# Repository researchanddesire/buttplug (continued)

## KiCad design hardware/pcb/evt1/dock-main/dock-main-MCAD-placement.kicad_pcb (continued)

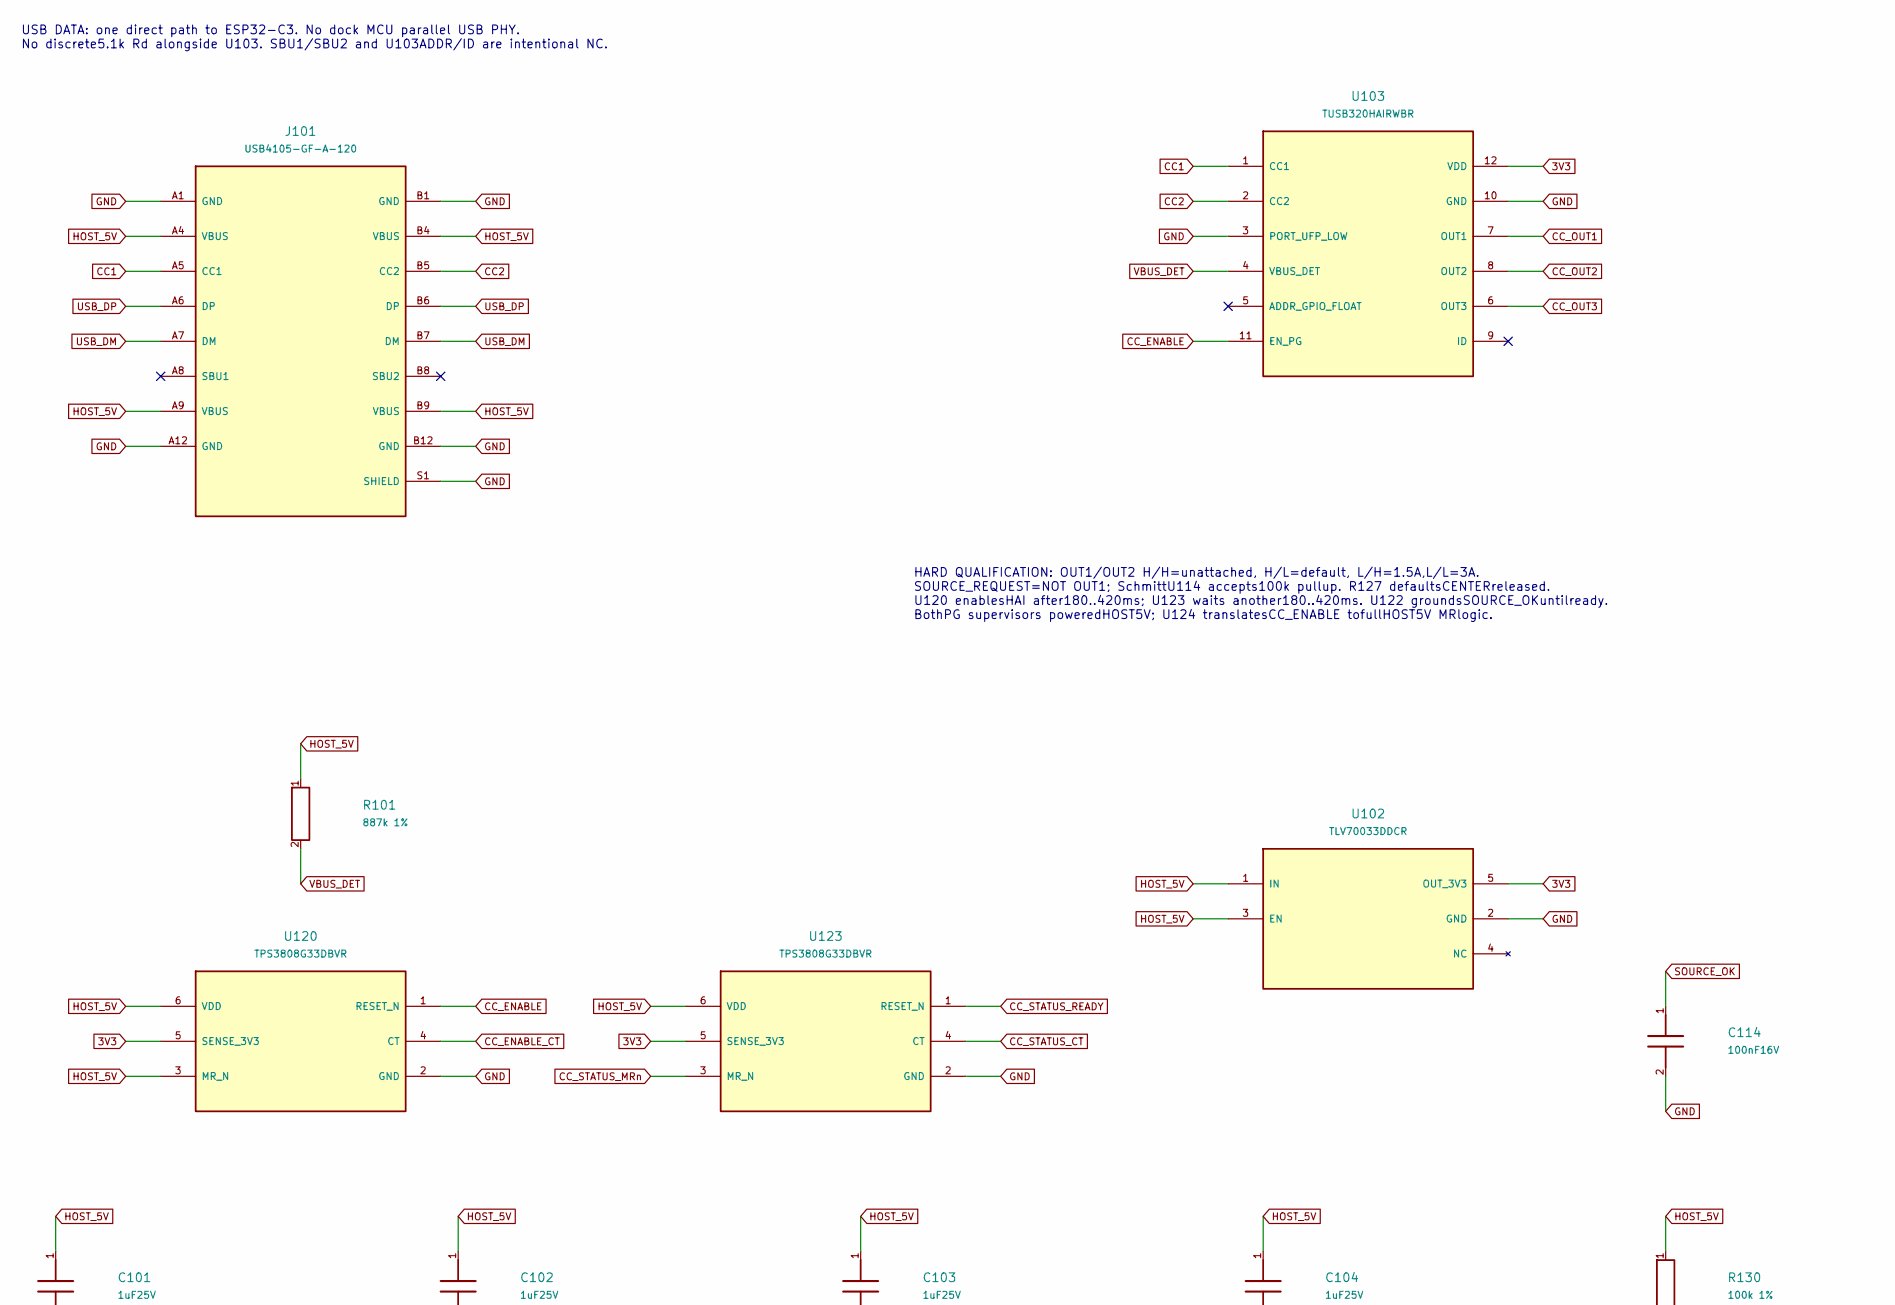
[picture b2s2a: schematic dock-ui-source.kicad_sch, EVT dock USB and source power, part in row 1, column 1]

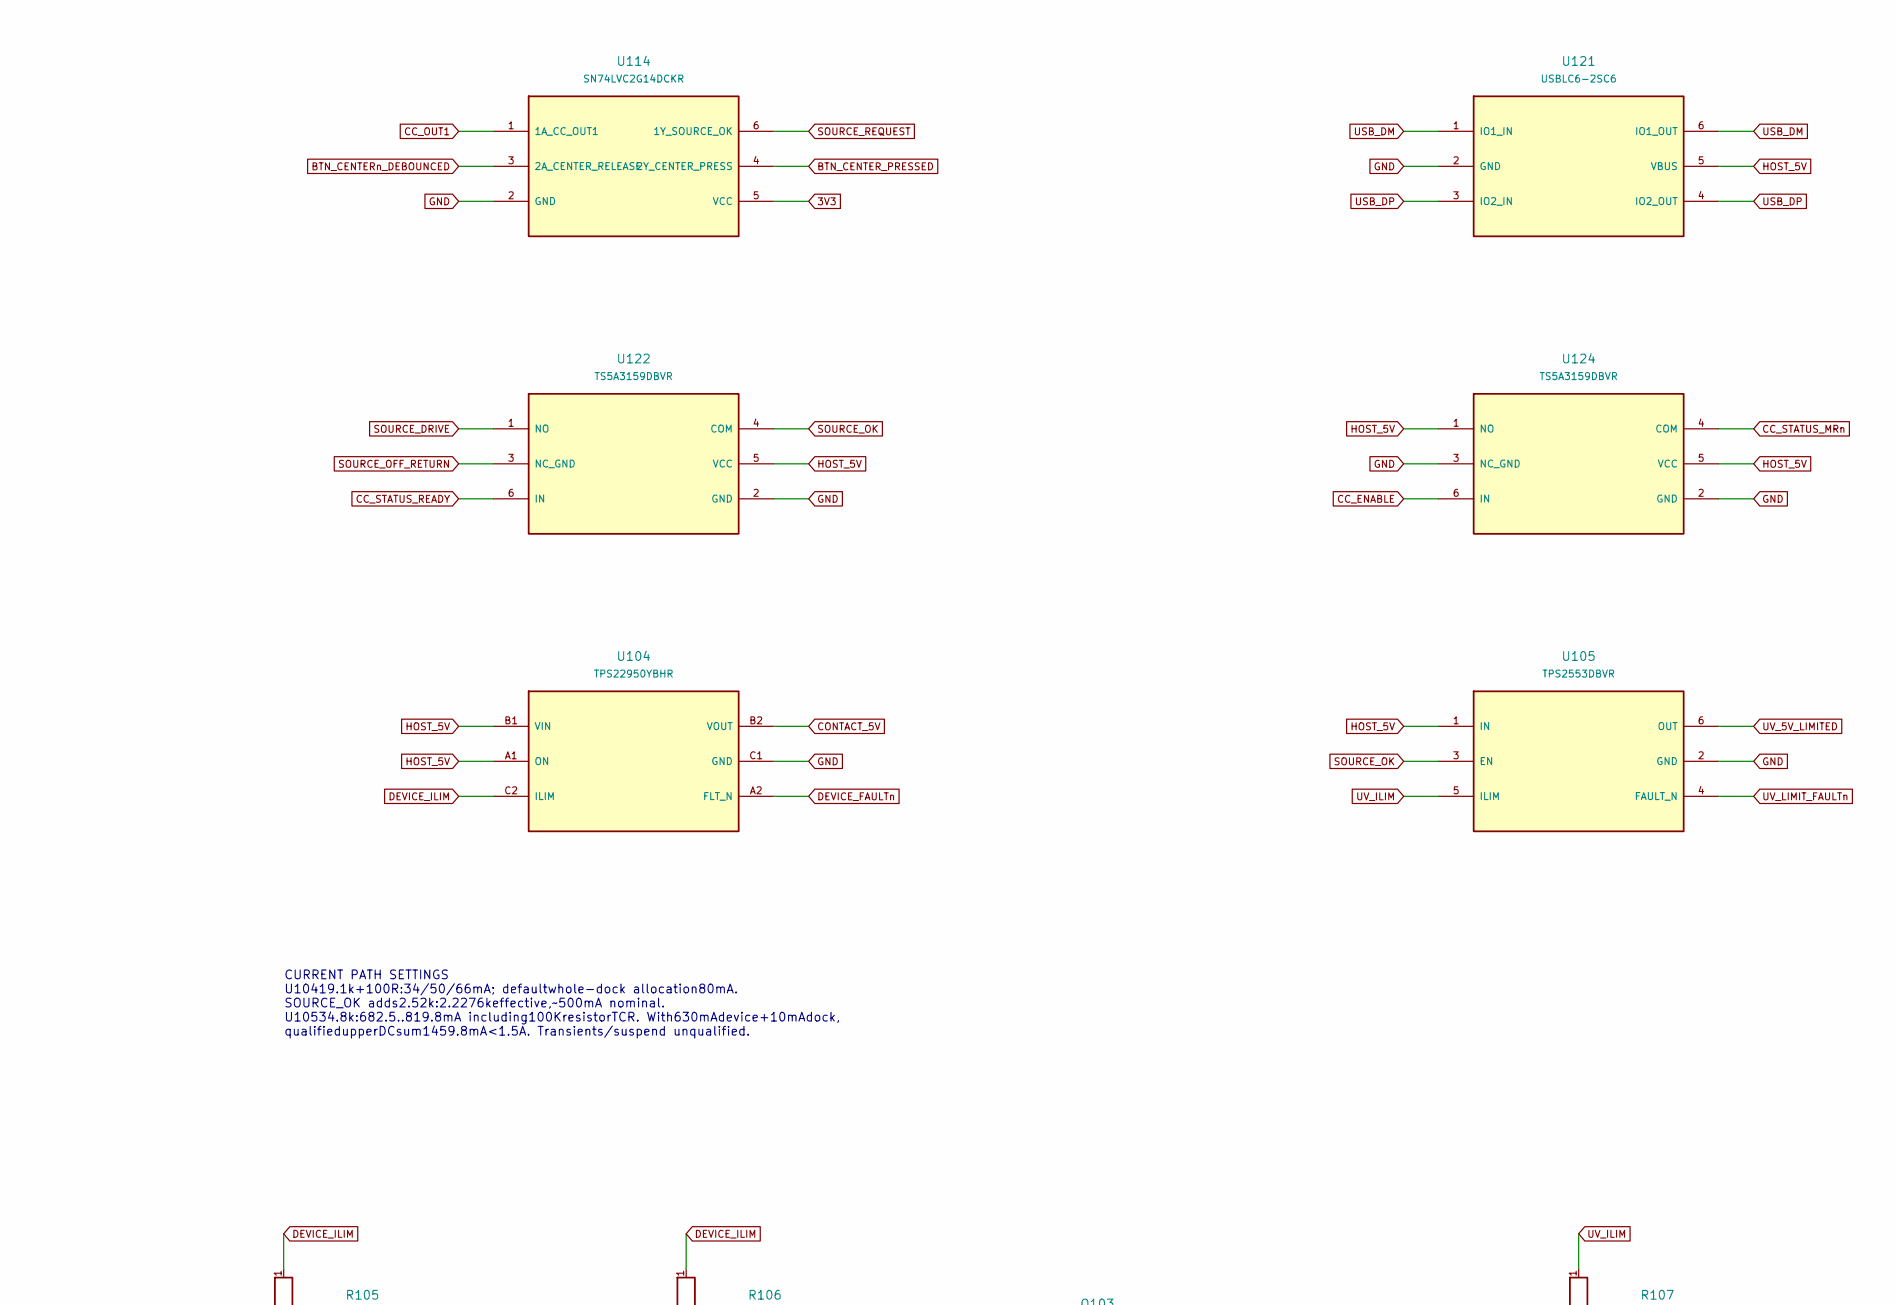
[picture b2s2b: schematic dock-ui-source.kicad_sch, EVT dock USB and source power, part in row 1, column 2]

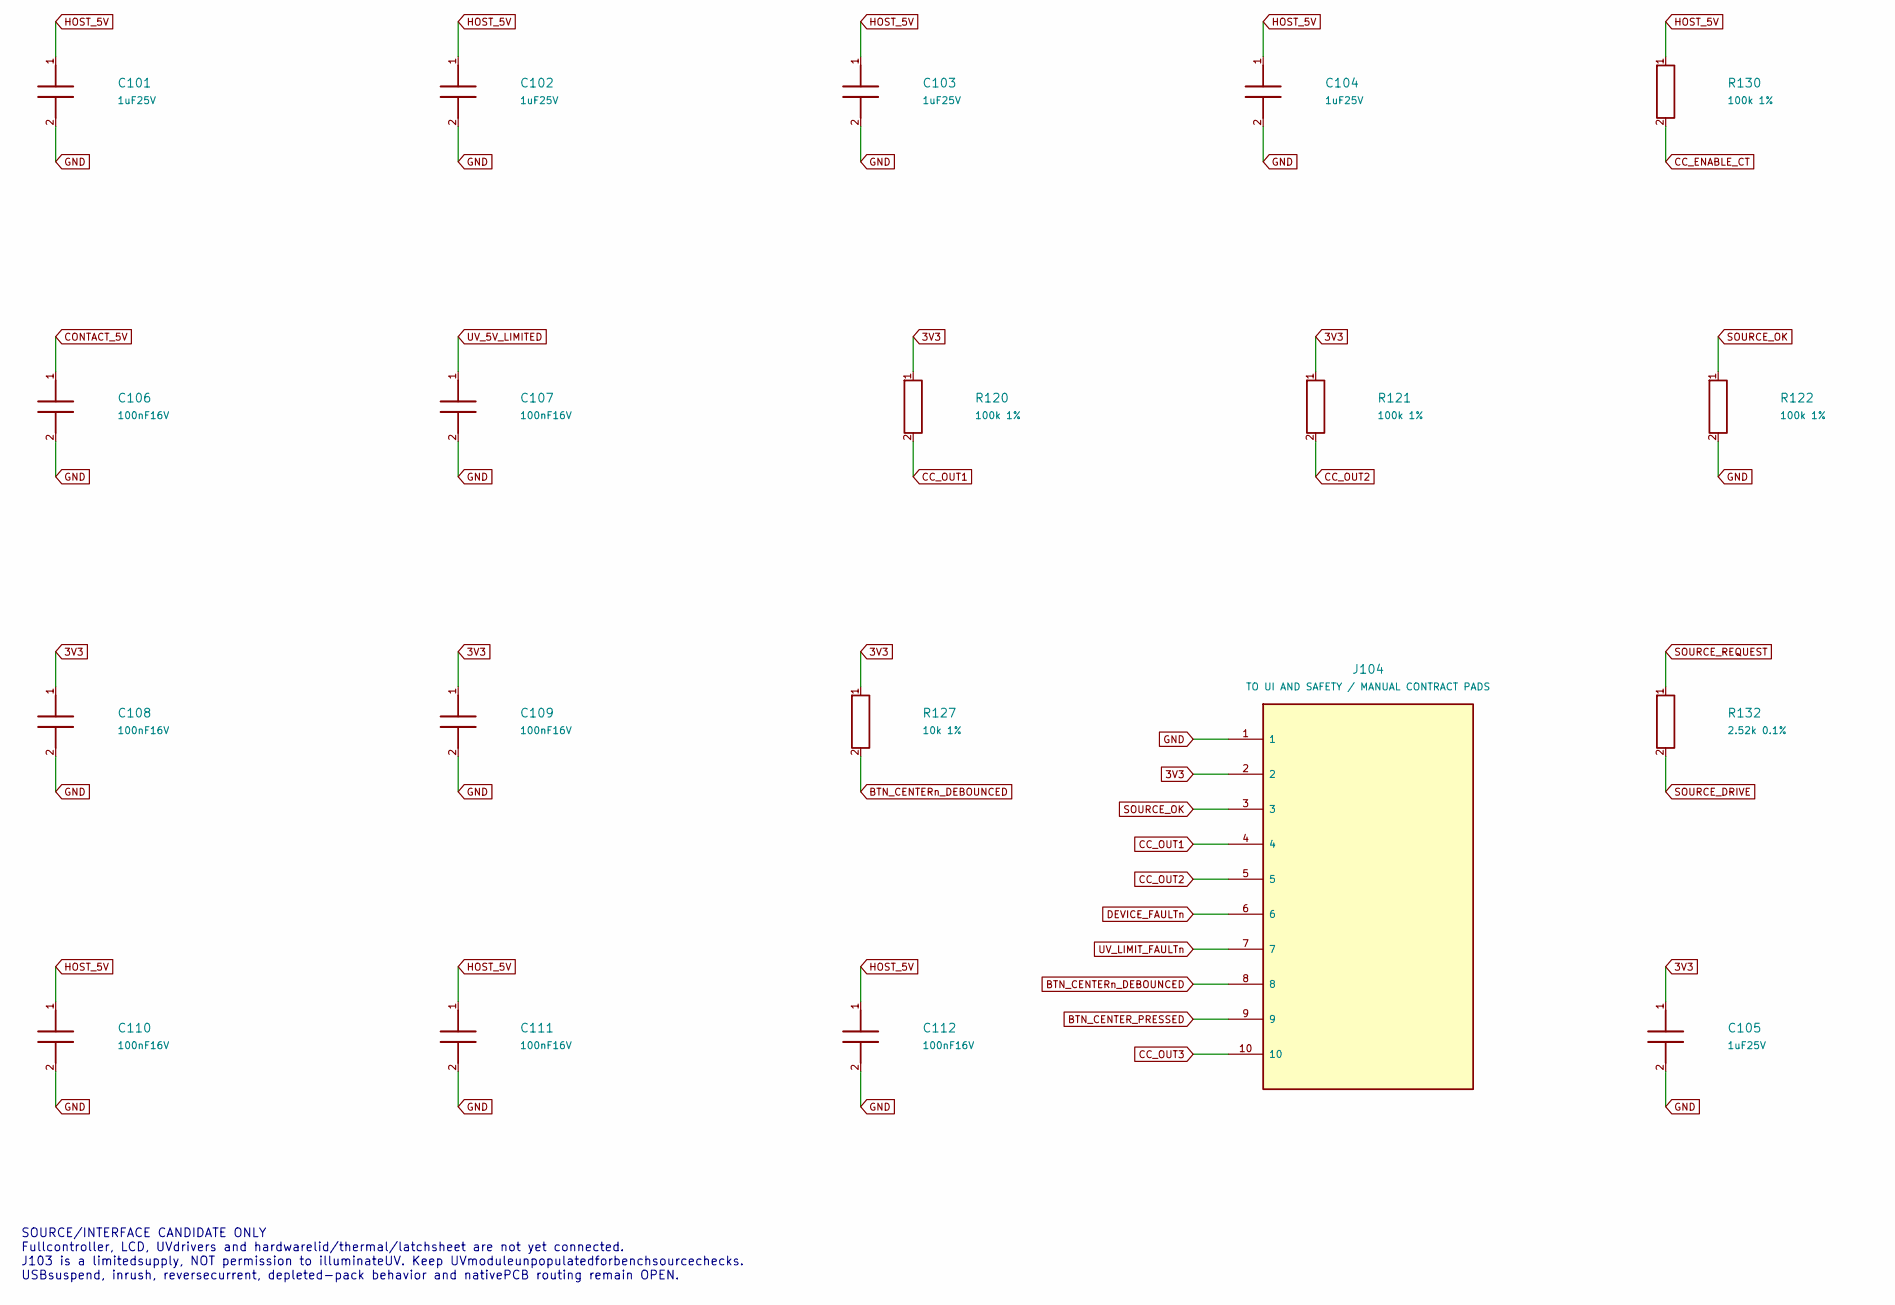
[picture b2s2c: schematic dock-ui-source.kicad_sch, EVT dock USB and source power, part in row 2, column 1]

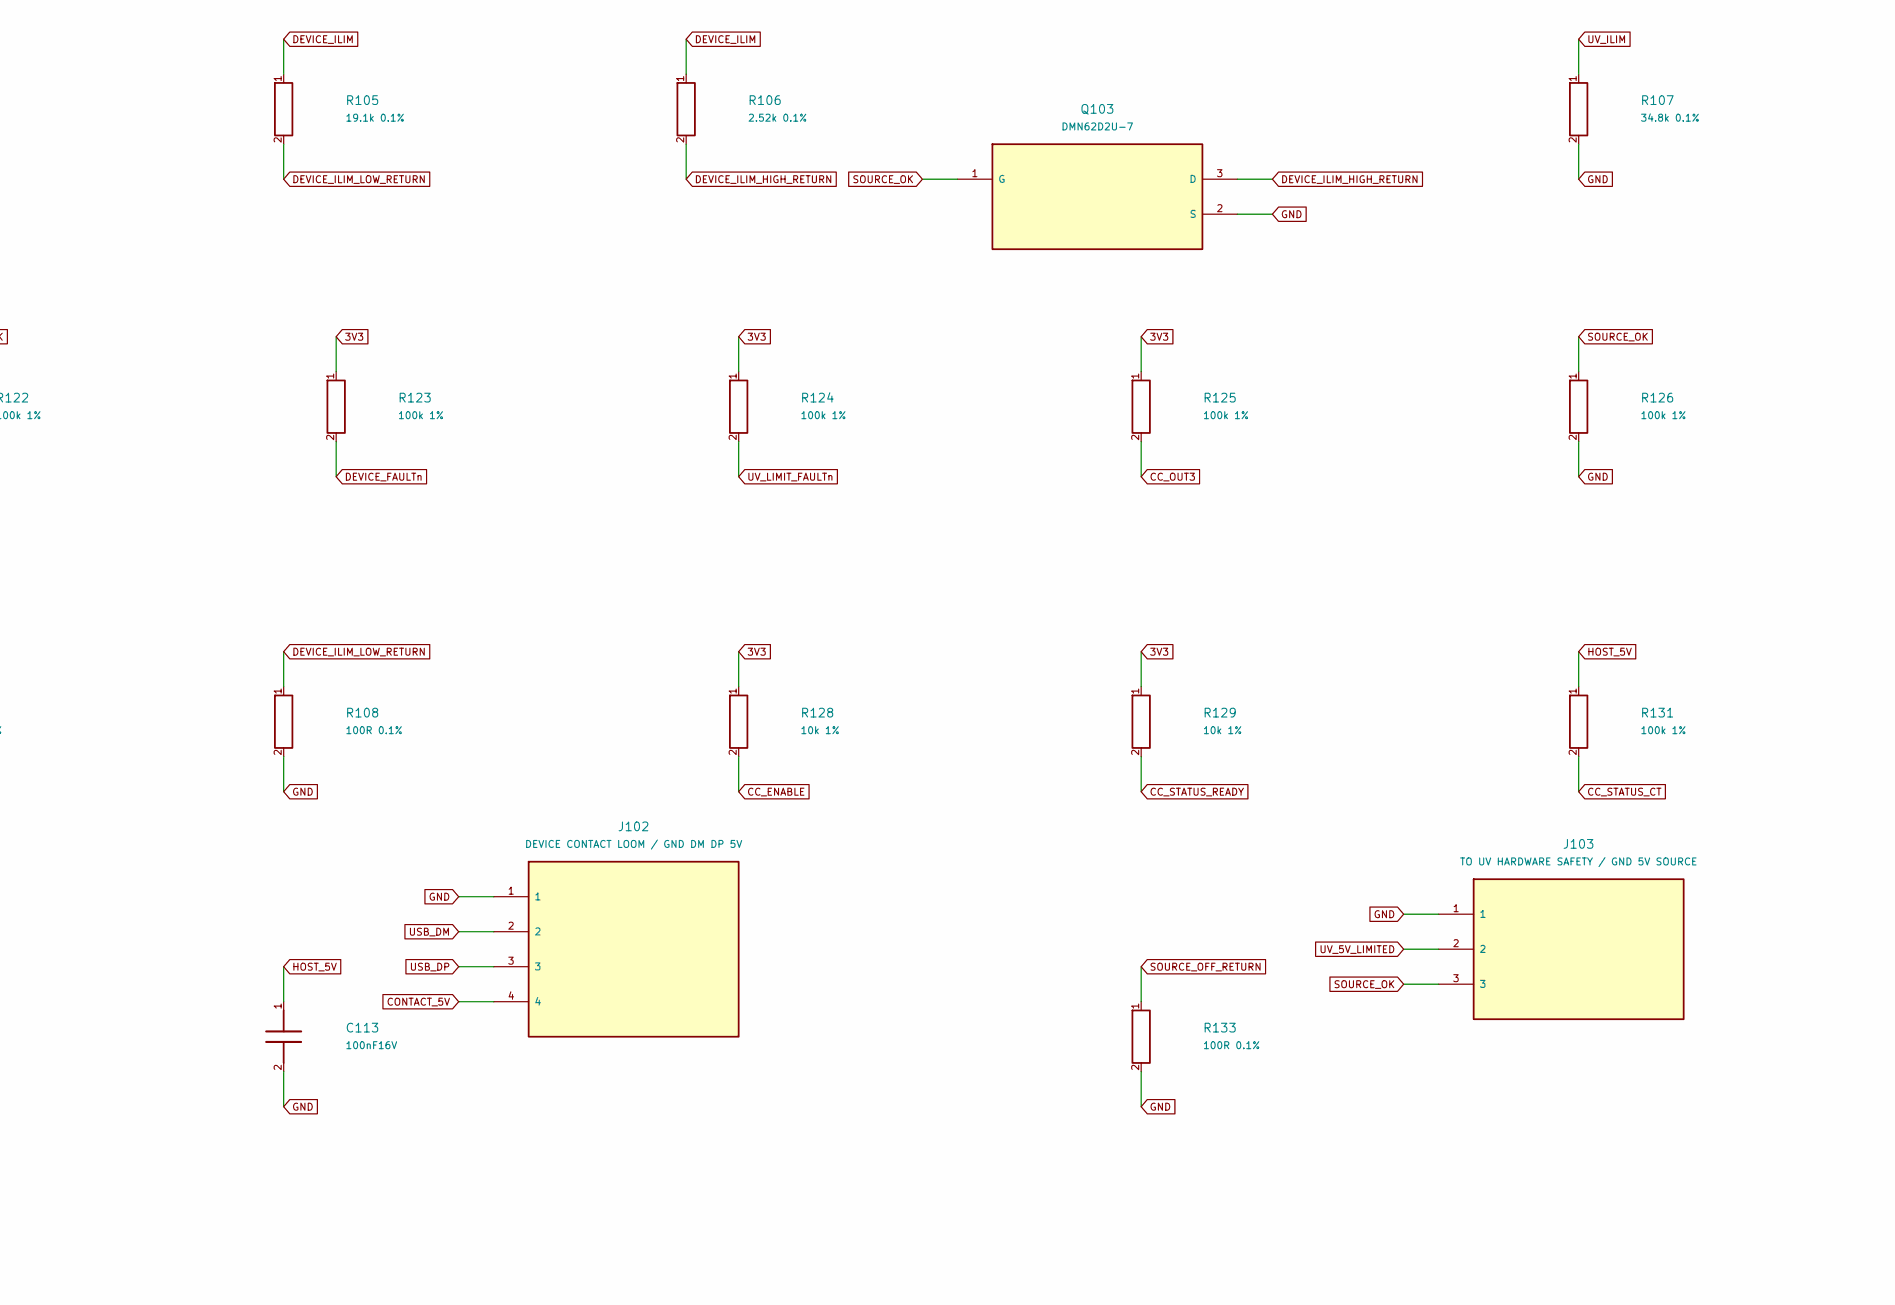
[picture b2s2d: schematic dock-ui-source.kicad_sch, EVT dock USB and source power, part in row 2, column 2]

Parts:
C101, C102, C103, C104, C105: 1uF25V; C_0603_1608Metric; MPN C1608X7R1E105K080AB
C106, C107, C108, C109, C110, C111, C112, C113, C114: 100nF16V; C_0402_1005Metric; MPN GRM155R71C104KA88D
J101: USB4105-GF-A-120; USB_C_Receptacle_GCT_USB4105-xx-A_16P_TopMnt_Horizontal; MPN USB4105-GF-A-120
J102: DEVICE CONTACT LOOM / GND DM DP 5V; Contact_Loom_4Land; MPN DEVICE CONTACT LOOM / GND DM DP 5V
J103: TO UV HARDWARE SAFETY / GND 5V SOURCE; Control_Loom_3Land; MPN TO UV HARDWARE SAFETY / GND 5V SOURCE
J104: TO UI AND SAFETY / MANUAL CONTRACT PADS; Control_Loom_10Land; MPN TO UI AND SAFETY / MANUAL CONTRACT PADS
Q103: DMN62D2U-7; SOT-23; MPN DMN62D2U-7
R101: 887k 1%; R_0603_1608Metric; MPN RC0603FR-07887KL
R105: 19.1k 0.1%; R_0603_1608Metric; MPN RT0603BRD0719K1L
R106, R132: 2.52k 0.1%; R_0603_1608Metric; MPN RT0603BRD072K52L
R107: 34.8k 0.1%; R_0603_1608Metric; MPN RT0603BRD0734K8L
R108, R133: 100R 0.1%; R_0603_1608Metric; MPN RT0603BRD07100RL
R120, R121, R122, R123, R124, R125, R126, R130, R131: 100k 1%; R_0603_1608Metric; MPN RC0603FR-07100KL
R127, R128, R129: 10k 1%; R_0603_1608Metric; MPN RC0603FR-0710KL
U102: TLV70033DDCR; TSOT-23-5; MPN TLV70033DDCR
U103: TUSB320HAIRWBR; Texas_X2QFN-12_1.6x1.6mm_P0.4mm; MPN TUSB320HAIRWBR
U104: TPS22950YBHR; Texas_YBH0006-C02_DSBGA-6_1.106x0.706mm_P0.4mm; MPN TPS22950YBHR
U105: TPS2553DBVR; SOT-23-6; MPN TPS2553DBVR
U114: SN74LVC2G14DCKR; SOT-363_SC-70-6; MPN SN74LVC2G14DCKR
U120, U123: TPS3808G33DBVR; SOT-23-6; MPN TPS3808G33DBVR
U121: USBLC6-2SC6; SOT-23-6; MPN USBLC6-2SC6
U122, U124: TS5A3159DBVR; SOT-23-6; MPN TS5A3159DBVR

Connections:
3V3: C105.1, C108.1, C109.1, J104.2, R120.1, R121.1, R123.1, R124.1, R125.1, R127.1, R128.1, R129.1, U102.5 (OUT_3V3), U103.12 (VDD), U114.5 (VCC), U120.5 (SENSE_3V3), U123.5 (SENSE_3V3); also elsewhere on the board
BTN_CENTER_PRESSED: J104.9, U114.4 (2Y_CENTER_PRESS); also elsewhere on the board
BTN_CENTERn_DEBOUNCED: J104.8, R127.2, U114.3 (2A_CENTER_RELEASE); also elsewhere on the board
CC1: J101.A5 (CC1), U103.1 (CC1)
CC2: J101.B5 (CC2), U103.2 (CC2)
CC_ENABLE: R128.2, U103.11 (EN_PG), U120.1 (RESET_N), U124.6 (IN)
CC_ENABLE_CT: R130.2, U120.4 (CT)
CC_OUT1: J104.4, R120.2, U103.7 (OUT1), U114.1 (1A_CC_OUT1); also elsewhere on the board
CC_OUT2: J104.5, R121.2, U103.8 (OUT2); also elsewhere on the board
CC_OUT3: J104.10, R125.2, U103.6 (OUT3)
CC_STATUS_CT: R131.2, U123.4 (CT)
CC_STATUS_MRn: U123.3 (MR_N), U124.4 (COM)
CC_STATUS_READY: R129.2, U122.6 (IN), U123.1 (RESET_N)
CONTACT_5V: C106.1, J102.4, U104.B2 (VOUT)
DEVICE_FAULTn: J104.6, R123.2, U104.A2 (FLT_N); also elsewhere on the board
DEVICE_ILIM: R105.1, R106.1, U104.C2 (ILIM)
DEVICE_ILIM_HIGH_RETURN: Q103.3 (D), R106.2
DEVICE_ILIM_LOW_RETURN: R105.2, R108.1
GND: C101.2, C102.2, C103.2, C104.2, C105.2, C106.2, C107.2, C108.2, C109.2, C110.2, C111.2, C112.2, C113.2, C114.2, J101.A1 (GND), J101.A12 (GND), J101.B1 (GND), J101.B12 (GND), J101.S1 (SHIELD), J102.1, J103.1, J104.1, Q103.2 (S), R107.2, R108.2, R122.2, R126.2, R133.2, U102.2 (GND), U103.3 (PORT_UFP_LOW), U103.10 (GND), U104.C1 (GND), U105.2 (GND), U114.2 (GND), U120.2 (GND), U121.2 (GND), U122.2 (GND), U123.2 (GND), U124.2 (GND), U124.3 (NC_GND); also elsewhere on the board
HOST_5V: C101.1, C102.1, C103.1, C104.1, C110.1, C111.1, C112.1, C113.1, J101.A4 (VBUS), J101.A9 (VBUS), J101.B4 (VBUS), J101.B9 (VBUS), R101.1, R130.1, R131.1, U102.1 (IN), U102.3 (EN), U104.A1 (ON), U104.B1 (VIN), U105.1 (IN), U120.3 (MR_N), U120.6 (VDD), U121.5 (VBUS), U122.5 (VCC), U123.6 (VDD), U124.1 (NO), U124.5 (VCC); also elsewhere on the board
SOURCE_DRIVE: R132.2, U122.1 (NO)
SOURCE_OFF_RETURN: R133.1, U122.3 (NC_GND)
SOURCE_OK: C114.1, J103.3, J104.3, Q103.1 (G), R122.1, R126.1, U105.3 (EN), U122.4 (COM); also elsewhere on the board
SOURCE_REQUEST: R132.1, U114.6 (1Y_SOURCE_OK)
USB_DM: J101.A7 (DM), J101.B7 (DM), J102.2, U121.1 (IO1_IN), U121.6 (IO1_OUT)
USB_DP: J101.A6 (DP), J101.B6 (DP), J102.3, U121.3 (IO2_IN), U121.4 (IO2_OUT)
UV_5V_LIMITED: C107.1, J103.2, U105.6 (OUT); also elsewhere on the board
UV_ILIM: R107.1, U105.5 (ILIM)
UV_LIMIT_FAULTn: J104.7, R124.2, U105.4 (FAULT_N); also elsewhere on the board
VBUS_DET: R101.2, U103.4 (VBUS_DET)

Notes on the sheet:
USB DATA: one direct path to ESP32-C3. No dock MCU parallel USB PHY. No discrete5.1k Rd alongside U103. SBU1/SBU2 and U103ADDR/ID are intentional NC.
HARD QUALIFICATION: OUT1/OUT2 H/H=unattached, H/L=default, L/H=1.5A,L/L=3A. SOURCE_REQUEST=NOT OUT1; SchmittU114 accepts100k pullup. R127 defaultsCENTERreleased. U120 enablesHAI after180..420ms; U123 waits another180..420ms. U122 groundsSOURCE_OKuntilready. BothPG supervisors poweredHOST5V; U124 tr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
CURRENT PATH SETTINGS U10419.1k+100R:34/50/66mA; defaultwhole-dock allocation80mA. SOURCE_OK adds2.52k:2.2276keffective,~500mA nominal. U10534.8k:682.5..819.8mA including100KresistorTCR. With630mAdevice+10mAdock, qualifiedupperDCsum1459.8mA<1.5A. Transients/suspend unqualified.
SOURCE/INTERFACE CANDIDATE ONLY Fullcontroller, LCD, UVdrivers and hardwarelid/thermal/latchsheet are not yet connected. J103 is a limitedsupply, NOT permission to illuminateUV. Keep UVmoduleunpopulatedforbenchsourcechecks. USBsuspend, inrush, reversecurrent, depleted-pack behavior and nativePCB ro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

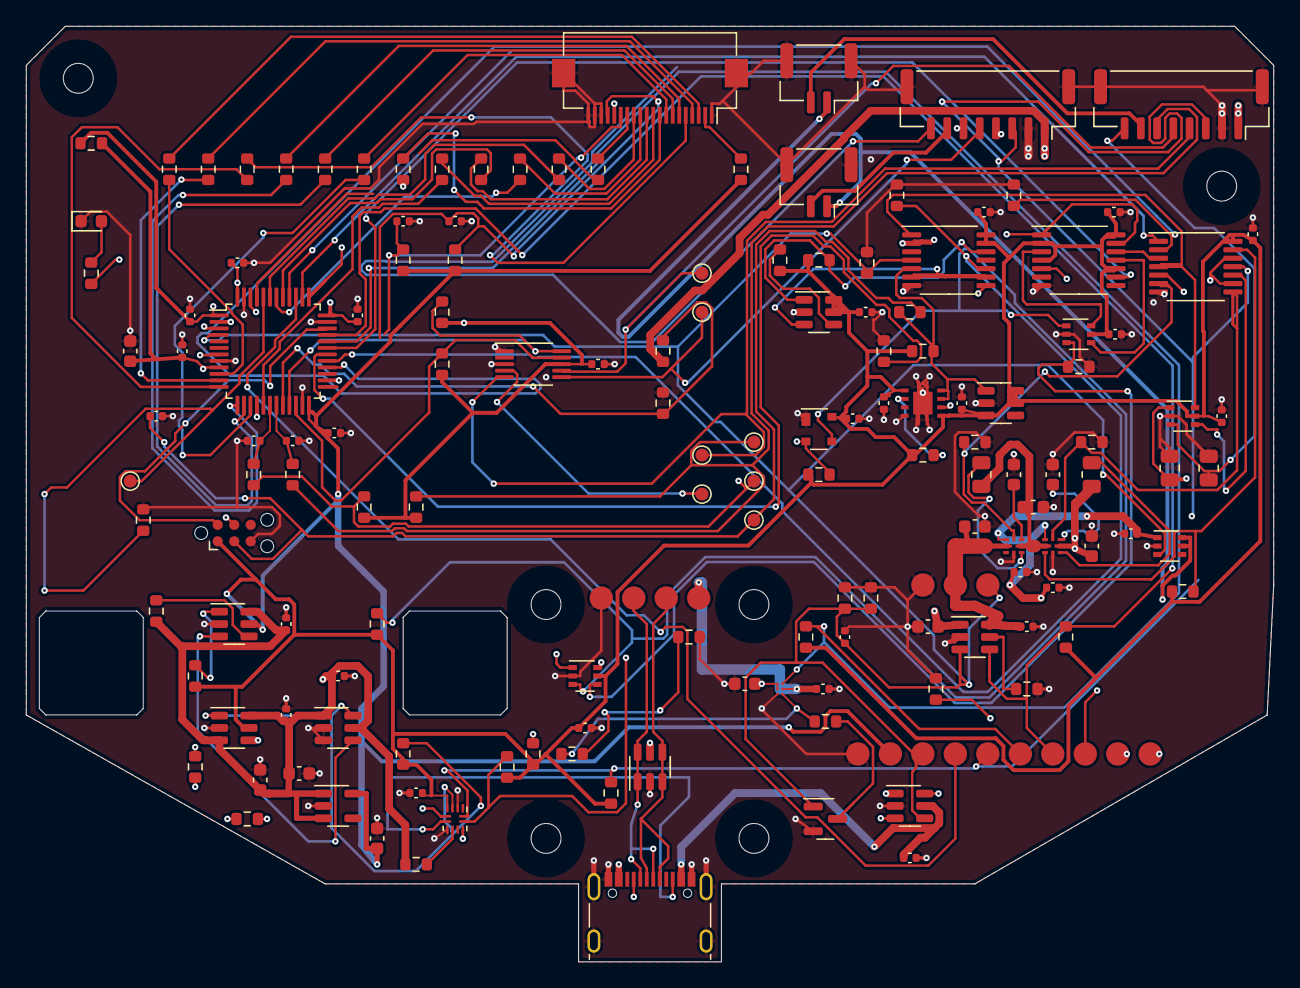
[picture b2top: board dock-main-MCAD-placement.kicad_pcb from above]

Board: 4 copper layers, 96.0 x 72.0 mm, 156 parts (0 on the bottom side), 107 nets.

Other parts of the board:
H701, H702, H703, H704, H705, H706: M2clearance2.3

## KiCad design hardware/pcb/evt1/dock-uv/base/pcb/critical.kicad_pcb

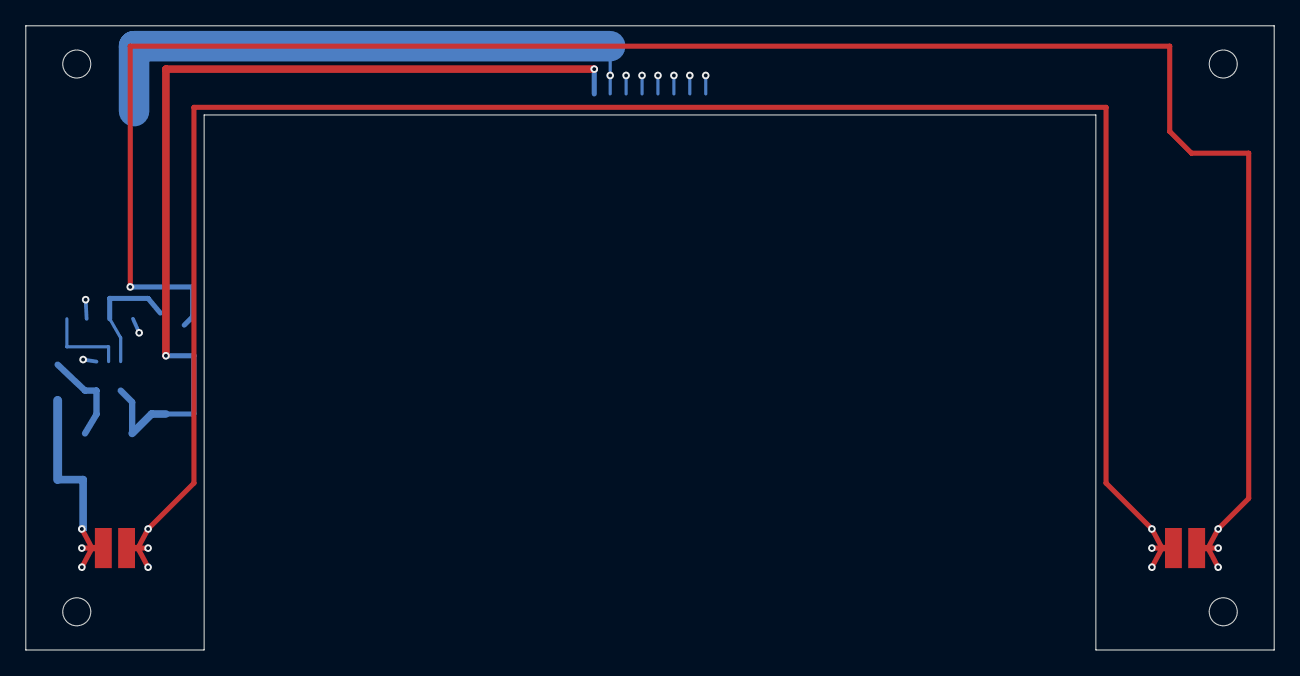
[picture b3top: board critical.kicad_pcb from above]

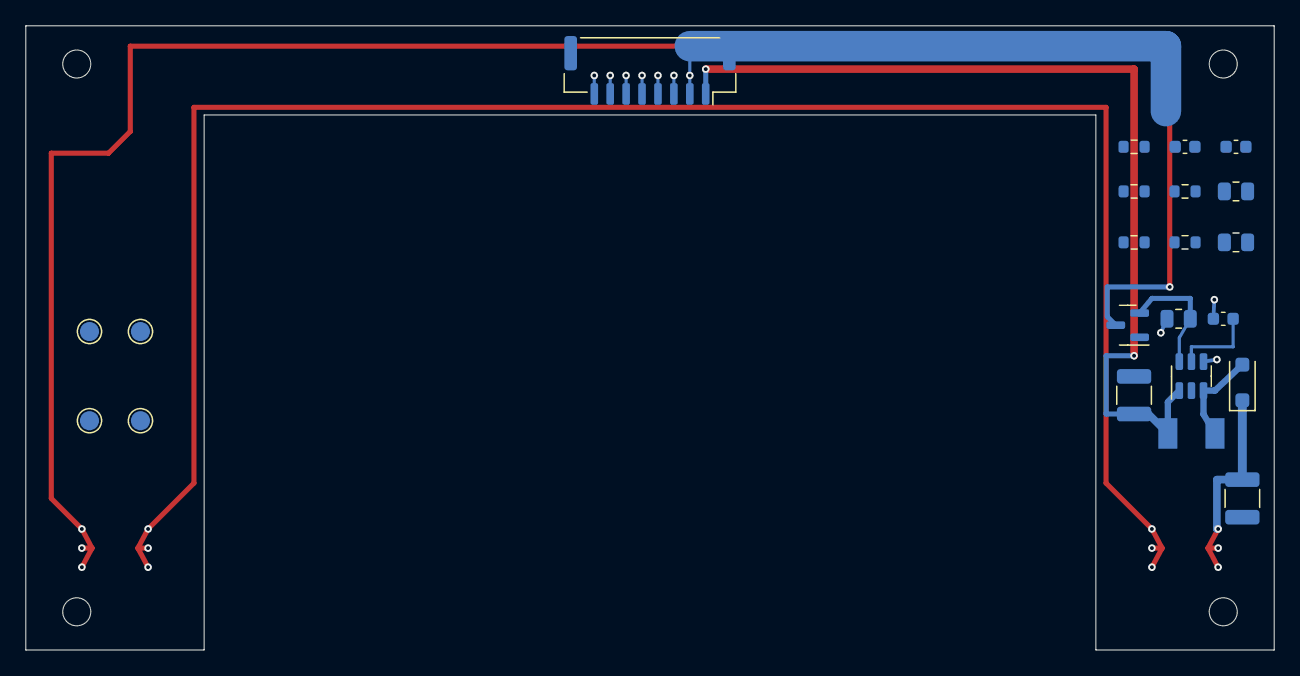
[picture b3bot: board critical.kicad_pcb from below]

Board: 2 copper layers, 98.0 x 49.0 mm, 28 parts (22 on the bottom side), 16 nets.

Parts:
C401, C402: 4.7uF50VX7R; C_1210_3225Metric
C403: 220nF25VX7R; C_0603_1608Metric
C404, C405: 100nF25VX7R; C_0603_1608Metric
D401: PMEG6010CEH,115; D_SOD-123F
D402, D403: VLMU35CB20-275-120; Vishay_VLMU35CB2_Actual_TwoTerminal
H401, H402, H403, H404: MountingHole_2.2mm_M2
J401: SM08B-GHS-TB; JST_GH_SM08B-GHS-TB_1x08-1MP_P1.25mm_Horizontal
L401: 10uH20% shielded; Bourns_SRP4020TA_Actual_Lands
Q401: DMN62D2U-7; SOT-23
R401: 3.65R1%100ppm; R_0805_2012Metric
R402: 1k1%; R_0603_1608Metric
R403: 100k1%; R_0603_1608Metric
R404: 100k1%; R_0805_2012Metric
R405: 1M1%; R_0805_2012Metric
R406: 68k1%; R_0603_1608Metric
R407, R408: 10k1%; R_0603_1608Metric
TP401: NTC_BASE; TestPoint_Pad_D1.5mm
TP402: GND; TestPoint_Pad_D1.5mm
TP403: BASE_THERM_SEND; TestPoint_Pad_D1.5mm
TP404: LOOP_A_RAW; TestPoint_Pad_D1.5mm
U401: TPS61165DBVR; SOT-23-6

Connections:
BASE_CATHODE_GATE: Q401.1, R402.2, R403.1
BASE_COMP: C403.1, U401.5
BASE_FB: C404.1, J401.4, R408.2
BASE_FB_RAW: Q401.2, R401.1, R408.1, U401.6
BASE_LED_K: D403.1, Q401.3
BASE_LED_MID: D402.1, D403.2
BASE_SW: D401.2, L401.2, U401.3
BASE_THERM_SEND: J401.7, TP403.1
BASE_VOUT: C402.1, D401.1, D402.2, R404.1, R405.1
BASE_VOUT_DIV: C405.1, J401.5, R407.2
BASE_VOUT_SENSE: R405.2, R406.1, R407.1
GND: C401.2, C402.2, C403.2, C404.2, C405.2, J401.2, J401.MP, R401.2, R403.2, R404.2, R406.2, TP402.1, U401.4
LOOP_A_RAW: J401.8, TP404.1
NTC_BASE: J401.6, TP401.1
UV_5V_SW: C401.1, J401.1, L401.1, U401.1
UV_CTRL: J401.3, R402.1, U401.2

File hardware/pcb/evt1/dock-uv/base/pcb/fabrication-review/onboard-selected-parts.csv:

Reference,Manufacturer,MPN,Value,Footprint,PrimarySource,AssemblyNote
U401,Texas Instruments,TPS61165DBVR,TPS61165DBVR,DockUV:SOT-23-6,https://www.ti.com/lit/ds/symlink/tps61165.pdf,
L401,Bourns,SRP4020TA-100M,10uH20% shielded,DockUV:Bourns_SRP4020TA_Actual_Lands,https://www.bourns.com/docs/Product-Datasheets/SRP4020TA.pdf,
D401,Nexperia,"PMEG6010CEH,115","PMEG6010CEH,115",DockUV:D_SOD-123F,https://assets.nexperia.com/documents/data-sheet/PMEG6010CEH.pdf,"Exact orderable12NC934061056115,SOD123F_115,3000/reel: https://www.nexperia.com/product/PMEG6010CEH"
D402,Vishay,VLMU35CB20-275-120,VLMU35CB20-275-120,DockUV:Vishay_VLMU35CB2_Actual_TwoTerminal,https://www.vishay.com/docs/80232/vlmu35cb2x-275-120.pdf,Cathode mark must match pad1. Heatspreader/AlMCPCB must be qualified.
D403,Vishay,VLMU35CB20-275-120,VLMU35CB20-275-120,DockUV:Vishay_VLMU35CB2_Actual_TwoTerminal,https://www.vishay.com/docs/80232/vlmu35cb2x-275-120.pdf,
Q401,Diodes Incorporated,DMN62D2U-7,DMN62D2U-7,DockUV:SOT-23,https://www.diodes.com/datasheet/download/DMN62D2U.pdf,"Cathode disconnect separate from input cuts; source is FB, not GND."
J401,JST,SM08B-GHS-TB(LF)(SN),SM08B-GHS-TB,DockUV:JST_GH_SM08B-GHS-TB_1x08-1MP_P1.25mm_Horizontal,https://www.jst-mfg.com/product/pdf/eng/eGH.pdf,
R401,Vishay,CRCW08053R65FKEA,3.65R1%100ppm,DockUV:R_0805_2012Metric,https://www.vishay.com/docs/20035/dcrcwe3.pdf,
R402,Yageo,RC0603FR-071KL,1k1%,DockUV:R_0603_1608Metric,https://www.yageogroup.com/component-documentation/download/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,
R403,Yageo,RC0603FR-07100KL,100k1%,DockUV:R_0603_1608Metric,https://www.yageogroup.com/component-documentation/download/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,
R404,Yageo,RC0805FR-07100KL,100k1%,DockUV:R_0805_2012Metric,https://www.yageogroup.com/component-documentation/download/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,
R405,Yageo,RC0805FR-071ML,1M1%,DockUV:R_0805_2012Metric,https://www.yageogroup.com/component-documentation/download/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,
R406,Yageo,RC0603FR-0768KL,68k1%,DockUV:R_0603_1608Metric,https://www.yageogroup.com/component-documentation/download/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,
R407,Yageo,RC0603FR-0710KL,10k1%,DockUV:R_0603_1608Metric,https://www.yageogroup.com/component-documentation/download/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,
R408,Yageo,RC0603FR-0710KL,10k1%,DockUV:R_0603_1608Metric,https://www.yageogroup.com/component-documentation/download/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,
C401,TDK,C3225X7R1H475K250AB,4.7uF50VX7R,DockUV:C_1210_3225Metric,https://product.tdk.com/en/search/capacitor/ceramic/mlcc/inf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,"Require >=1uF effective over VIN4.3..5.25V/input or VOUT0..39V/output,temp,age. TI output recommendation1..10uF."
C402,TDK,C3225X7R1H475K250AB,4.7uF50VX7R,DockUV:C_1210_3225Metric,https://product.tdk.com/en/search/capacitor/ceramic/mlcc/inf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,"Require >=1uF effective over VIN4.3..5.25V/input or VOUT0..39V/output,temp,age. TI output recommendation1..10uF."
C403,TDK,C1608X7R1E224K080AC,220nF25VX7R,DockUV:C_0603_1608Metric,https://product.tdk.com/en/search/capacitor/ceramic/mlcc/inf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,
C404,TDK,C1608X7R1E104K080AA,100nF25VX7R,DockUV:C_0603_1608Metric,https://product.tdk.com/en/search/capacitor/ceramic/mlcc/inf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,
C405,TDK,C1608X7R1E104K080AA,100nF25VX7R,DockUV:C_0603_1608Metric,https://product.tdk.com/en/search/capacitor/ceramic/mlcc/inf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,
